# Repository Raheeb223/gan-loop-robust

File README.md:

# gan-loop-robust

**Open-source, verified extraction of GaN half-bridge PCB power-loop inductance, from KiCad layout to switching behaviour.**

This repository is the reproducibility package for the accompanying manuscript (under review).
It contains all code, input data, generated KiCad boards, result tables and figures. One
command regenerates every number, table and figure using only free tools:
**KiCad 10, FastHenry 2, openEMS 0.37, ngspice 47 and Python 3.14**.

One parametric layout description (`scripts/layouts.py`) generates both
* manufacturable 4-layer **KiCad boards** (DRC-clean, with Gerbers and drill files), and
* **solver models** for FastHenry (PEEC) and openEMS (FDTD) with identical copper.

An **ngspice** model of the EPC2015C, built only from its datasheet, turns the extracted
inductances into switching waveforms.

## Verification summary

| Tier | Reference | Result |
|---|---|---|
| 1a | Exact 2-D geometric-mean-distance solution; Grover bar formula | FastHenry within 0.02 % and 0.13 % (DC) |
| 1b | Published commercial FEA (Letellier *et al.*, IEEE TPEL 2018), three power loops | FastHenry within 0.9–2.6 % |
| 1c | openEMS full-wave FDTD (independent method) | within 0.4–5.2 % of FastHenry |
| 2  | EPC commercial simulation (WP010 / Reusch & Strydom), three layout families | optimal −1.2 %, vertical +2.5 % (31/4 mil); all trends reproduced |
| 3  | EPC measured overshoot (8 boards) | calibrated on one layout family, other two predicted: hold-out MAE 7.7 percentage points |

Known differences larger than 10 % between this work and published data, with their
assessment, are listed in [`results/discrepancies.md`](results/discrepancies.md).

## Extensions (coupled loops, tolerances, robust design, newer devices)

| Topic | Script(s) | Output |
|---|---|---|
| Calibration error surface, leave-one-family-out test, dv/dt definitions | `p2_crossval.py` | `results/phase2/` |
| Ringing-method sensitivity to the assumed input tolerance (±10/20/30 %) | `ring_sensitivity.py` | `results/revision/` |
| Coupled power + gate-loop extraction (3-port), Grover mutual-inductance check | `p3_extract.py` | `results/phase3/` |
| Passive RL ladder fit, K-coupled ngspice bench, false turn-on margin | `p3_spice.py` | `results/phase3/` |
| openEMS cross-check of the coupled extraction (6 FDTD runs) | `p3_openems.py` | `results/phase3/` |
| FastHenry campaign over design + fabrication-tolerance variables | `p4_campaign.py` | `results/phase4/campaign.csv` |
| Gaussian-process surrogate, split-conformal intervals, Sobol indices | `p4_uq.py` | `results/phase4/` |
| NSGA-II robust optimisation, FastHenry verification, KiCad boards | `p5_opt.py` | `results/phase5/`, `kicad/boards_p5/` |
| EPC2218 and EPC2302 (2026 datasheets): models, extraction, switching | `devices.py`, `p6_devices.py` | `results/phase6/` |

Fabrication tolerances are taken from the JLCPCB capabilities page where stated
(finished thickness ±10 %, PTH +0.13/−0.08 mm, hole position ±0.075 mm); the remaining
ones (copper thickness, bump height, die offset) are marked as assumptions in
`scripts/p4_campaign.py`.

## Requirements

* Windows 10/11 (the scripts are PowerShell; the Python code itself is portable)
* Python 3.14, Git, KiCad 10 (default install location)
* About 2 GB of free disk space. No administrator rights are needed.

## Quick start

```powershell
powershell -ExecutionPolicy Bypass -File setup.ps1     # venv, openEMS, ngspice, FastHenry build, baseline tool
powershell -ExecutionPolicy Bypass -File run_all.ps1   # every table and figure
powershell -ExecutionPolicy Bypass -File run_all.ps1 -SkipOpenEMS   # same, without the ~2 h FDTD cross-check
```

`setup.ps1` installs the pinned Python packages from `requirements.txt` and compiles FastHenry
from source using the `ziglang` pip package (see `scripts/build_fasthenry.ps1` for why it is a
32-bit build). Tool versions are recorded in `results/provenance.json` on every run.

## Where each result comes from

| Result | Script(s) | Output | Runtime* |
|---|---|---|---|
| Closed-form references | `analytic.py` | console | < 1 min |
| FastHenry vs published FEA | `canonical_fh.py` | `results/tables/canonical_fh.csv` | 5 min |
| openEMS vs FastHenry | `canonical_oems.py` | `results/tables/canonical_oems.csv` | ~2 h |
| Comparison with EPC simulation, high-frequency convergence | `sweep_epc.py`, `hf_ladder.py` | `epc_sweep_hf.csv`, `epc_mesh.csv`, `hf_ladder.csv` | 26 min |
| KiCad boards and DRC | `kicad_prims.py`, `kicad_all.py` | `kicad/boards/`, `kicad_drc.csv` | few min |
| Existing open extractor (baseline) | `bench_dcdc.py` | `dcdc_benchmark.csv` | 10 min |
| Bias and uncertainty of ringing-based inductance | `ring_uncertainty.py` | `ring_bias.csv`, `ring_mc.csv` | 1 min |
| Circuit-level validation against measured boards | `circuit_validation.py` | `circuit_validation.csv`, `circuit_calibration_grid.csv` | 6 min |
| Design map for standard fabrication stack-ups | `design_map.py`, `design_map_overshoot.py` | `design_map.csv`, `design_map_points.csv` | 13 min |
| Figures | `figures.py` | `results/figures/*.pdf, *.png` | < 1 min |

\*Measured on a 4-core Intel i5-1035G1 laptop with 12 GB RAM. Fixed seeds are used throughout;
re-running the pipeline reproduces the stored tables bit-for-bit (solver runtimes excepted).

## Repository layout

```
scripts/          all code; each file starts with a docstring explaining the method and assumptions
  analytic.py       closed-form references (Grover bar, exact 2-D loop, ringing formula)
  geom.py           solver-neutral copper geometry and FastHenry exporter
  oems.py           openEMS model builder and impedance extraction
  layouts.py        EPC-style lateral / vertical / optimal power loops (parametric)
  kicad_prims.py    manufacturable copper primitives; kicad_build.py -> .kicad_pcb
  epc_model.py      datasheet-derived EPC2015C ngspice model; spice_sim.py -> commutation bench
data/published/   every external number used, with source, location and confidence (see SOURCES.md)
results/tables/   every computed number (CSV)
results/figures/  figures (PDF and PNG)
kicad/boards/     16 generated boards with DRC reports and fabrication files
patches/          changes applied to the third-party baseline tool
```

## Third-party software

* **fl4p/dcdc-parasitics** (baseline extractor) is cloned by `setup.ps1` at commit
  `12962bb` and is not redistributed here. Two patches are applied:
  * `patches/dcdc-parasitics_kicad10.patch`: two one-line KiCad 10 API compatibility fixes
    (`PCB_VIA::GetWidth` needs a layer argument);
  * `patches/dcdc_diag_all_pad_terminals.patch`: a diagnostic variant in which every pad of
    a device net is connected (used only for the "all pads connected" column of the baseline
    comparison).
* FastHenry 2 (MIT-style licence), openEMS (GPL-3), ngspice (BSD) and KiCad (GPL-3) are
  downloaded or built by `setup.ps1` and keep their own licences.

## Source documents

Published values were transcribed or pixel-digitised from EPC application material and IEEE
papers. The source documents are copyrighted and not included. The digitised values are, so
every downstream result is reproducible without them. See
[`data/published/SOURCES.md`](data/published/SOURCES.md) to re-run the digitisation step.

## Licence

Code: [MIT](LICENSE). Generated data, tables, figures and board files:
[CC BY 4.0](LICENSE-DATA).

## Citation

See [`CITATION.cff`](CITATION.cff). A DOI will be added on publication.

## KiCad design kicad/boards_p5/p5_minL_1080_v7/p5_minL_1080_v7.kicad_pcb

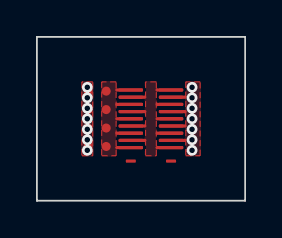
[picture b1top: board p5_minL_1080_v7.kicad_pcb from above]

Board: 4 copper layers, 11.6 x 9.1 mm, 6 parts (0 on the bottom side), 3 nets.

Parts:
C1, C2, C3, C4: 1uF 0402
Q_S: EPC2015C
Q_T: EPC2015C

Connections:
GND: C1.1, C2.1, C3.1, C4.1, Q_S.4, Q_S.6, Q_S.8, Q_S.10
SW: Q_S.3, Q_S.5, Q_S.7, Q_S.9, Q_S.11, Q_T.4, Q_T.6, Q_T.8, Q_T.10
VIN: C1.2, C2.2, C3.2, C4.2, Q_T.3, Q_T.5, Q_T.7, Q_T.9, Q_T.11

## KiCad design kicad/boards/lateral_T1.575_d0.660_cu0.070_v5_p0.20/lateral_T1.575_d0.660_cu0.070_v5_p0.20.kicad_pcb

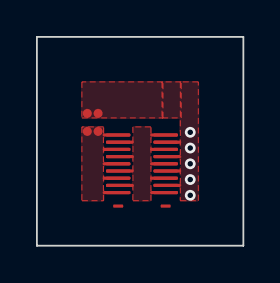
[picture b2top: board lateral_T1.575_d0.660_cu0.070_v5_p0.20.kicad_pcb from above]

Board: 4 copper layers, 11.5 x 11.6 mm, 4 parts (0 on the bottom side), 3 nets.

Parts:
C1, C2: 1uF 0402
Q_S: EPC2015C
Q_T: EPC2015C

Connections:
GND: C1.2, C2.2, Q_S.4, Q_S.6, Q_S.8, Q_S.10
SW: Q_S.3, Q_S.5, Q_S.7, Q_S.9, Q_S.11, Q_T.4, Q_T.6, Q_T.8, Q_T.10
VIN: C1.1, C2.1, Q_T.3, Q_T.5, Q_T.7, Q_T.9, Q_T.11

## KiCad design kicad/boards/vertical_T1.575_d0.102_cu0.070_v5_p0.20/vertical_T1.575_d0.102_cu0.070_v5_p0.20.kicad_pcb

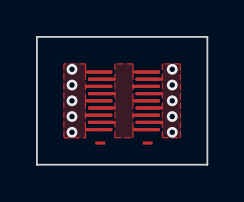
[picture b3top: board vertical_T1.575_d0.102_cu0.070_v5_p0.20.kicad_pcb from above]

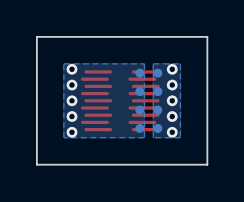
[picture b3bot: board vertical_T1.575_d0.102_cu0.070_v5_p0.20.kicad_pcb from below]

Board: 4 copper layers, 9.5 x 7.1 mm, 6 parts (4 on the bottom side), 3 nets.

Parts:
C1, C2, C3, C4: 1uF 0402
Q_S: EPC2015C
Q_T: EPC2015C

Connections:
GND: C1.2, C2.2, C3.2, C4.2, Q_S.4, Q_S.6, Q_S.8, Q_S.10
SW: Q_S.3, Q_S.5, Q_S.7, Q_S.9, Q_S.11, Q_T.4, Q_T.6, Q_T.8, Q_T.10
VIN: C1.1, C2.1, C3.1, C4.1, Q_T.3, Q_T.5, Q_T.7, Q_T.9, Q_T.11
